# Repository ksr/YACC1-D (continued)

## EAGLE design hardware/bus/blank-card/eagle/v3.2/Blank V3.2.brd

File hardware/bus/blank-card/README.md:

# bus/blank-card

Starting point for a new card: the bus connector(s), card outline and mounting, with every bus signal named.
`eagle/v3.1/` (2020-08-23) = the Bus Template V3.1 schematic on the card outline; ordered 2025-06-27 as a bare
board (zip + Fusion CAM output in `fab/`) and used as the base of the video card.

**Caution:** it carries the Bus V3.1 signal names, i.e. C3–C6 are labelled -ADDR-REG-RD0/LD0/RD1/LD1. The machine
is built to Bus V3.2, where those pins are ADDR-REG-ID0..3 (see `hardware/FABRICATED.md` notes and
`docs/system/`). Any card drawn on this template inherits the stale names (Mem Switch, Mem Register and the video
card did). `eagle/v3.2/` (derived 2026-09-20, see its README) is V3.1 with those four nets renamed to the V3.2 names: **start new cards from V3.2.**

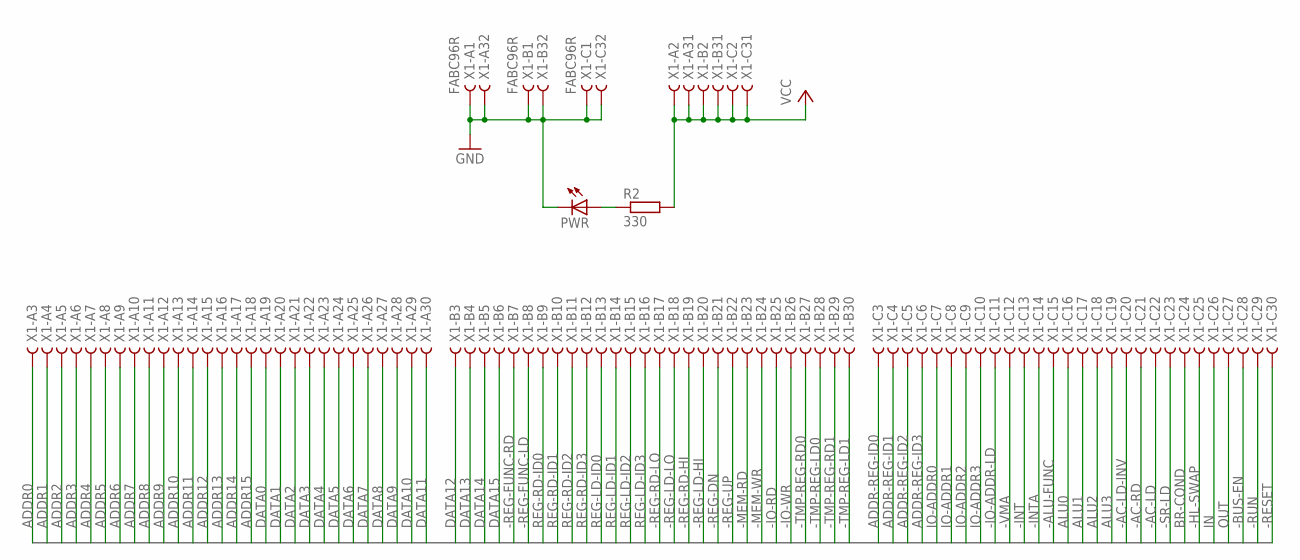
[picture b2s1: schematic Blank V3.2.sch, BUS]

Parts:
PWR: LED5MM
R2: 330; 0207/10
X1: FABC96R

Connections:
-AC-LD: X1.C22
-AC-LD-INV: X1.C20
-AC-RD: X1.C21
-ALU-FUNC: X1.C15
-BUS-EN: X1.C28
-HL-SWAP: X1.C25
-INT: X1.C13
-INTA: X1.C14
-IO-ADDR-LD: X1.C11
-IO-RD: X1.B25
-IO-WR: X1.B26
-MEM-RD: X1.B23
-MEM-WR: X1.B24
-REG-DN: X1.B21
-REG-FUNC-LD: X1.B8
-REG-FUNC-RD: X1.B7
-REG-LD-HI: X1.B20
-REG-LD-LO: X1.B18
-REG-RD-HI: X1.B19
-REG-RD-LO: X1.B17
-REG-UP: X1.B22
-RESET: X1.C30
-RUN: X1.C29
-SR-LD: X1.C23
-TMP-REG-LD0: X1.B28
-TMP-REG-LD1: X1.B30
-TMP-REG-RD0: X1.B27
-TMP-REG-RD1: X1.B29
-VMA: X1.C12
ADDR0: X1.A3
ADDR1: X1.A4
ADDR2: X1.A5
ADDR3: X1.A6
ADDR4: X1.A7
ADDR5: X1.A8
ADDR6: X1.A9
ADDR7: X1.A10
ADDR8: X1.A11
ADDR9: X1.A12
ADDR10: X1.A13
ADDR11: X1.A14
ADDR12: X1.A15
ADDR13: X1.A16
ADDR14: X1.A17
ADDR15: X1.A18
ADDR-REG-ID0: X1.C3
ADDR-REG-ID1: X1.C4
ADDR-REG-ID2: X1.C5
ADDR-REG-ID3: X1.C6
ALU0: X1.C16
ALU1: X1.C17
ALU2: X1.C18
ALU3: X1.C19
BR-COND: X1.C24
DATA0: X1.A19
DATA1: X1.A20
DATA2: X1.A21
DATA3: X1.A22
DATA4: X1.A23
DATA5: X1.A24
DATA6: X1.A25
DATA7: X1.A26
DATA8: X1.A27
DATA9: X1.A28
DATA10: X1.A29
DATA11: X1.A30
DATA12: X1.B3
DATA13: X1.B4
DATA14: X1.B5
DATA15: X1.B6
GND: PWR.K (C), X1.A1, X1.A32, X1.B1, X1.B32, X1.C1, X1.C32
IN: X1.C26
IO-ADDR0: X1.C7
IO-ADDR1: X1.C8
IO-ADDR2: X1.C9
IO-ADDR3: X1.C10
unnamed: PWR.A, R2.1
OUT: X1.C27
REG-LD-ID0: X1.B13
REG-LD-ID1: X1.B14
REG-LD-ID2: X1.B15
REG-LD-ID3: X1.B16
REG-RD-ID0: X1.B9
REG-RD-ID1: X1.B10
REG-RD-ID2: X1.B11
REG-RD-ID3: X1.B12
VCC: R2.2, X1.A2, X1.A31, X1.B2, X1.B31, X1.C2, X1.C31

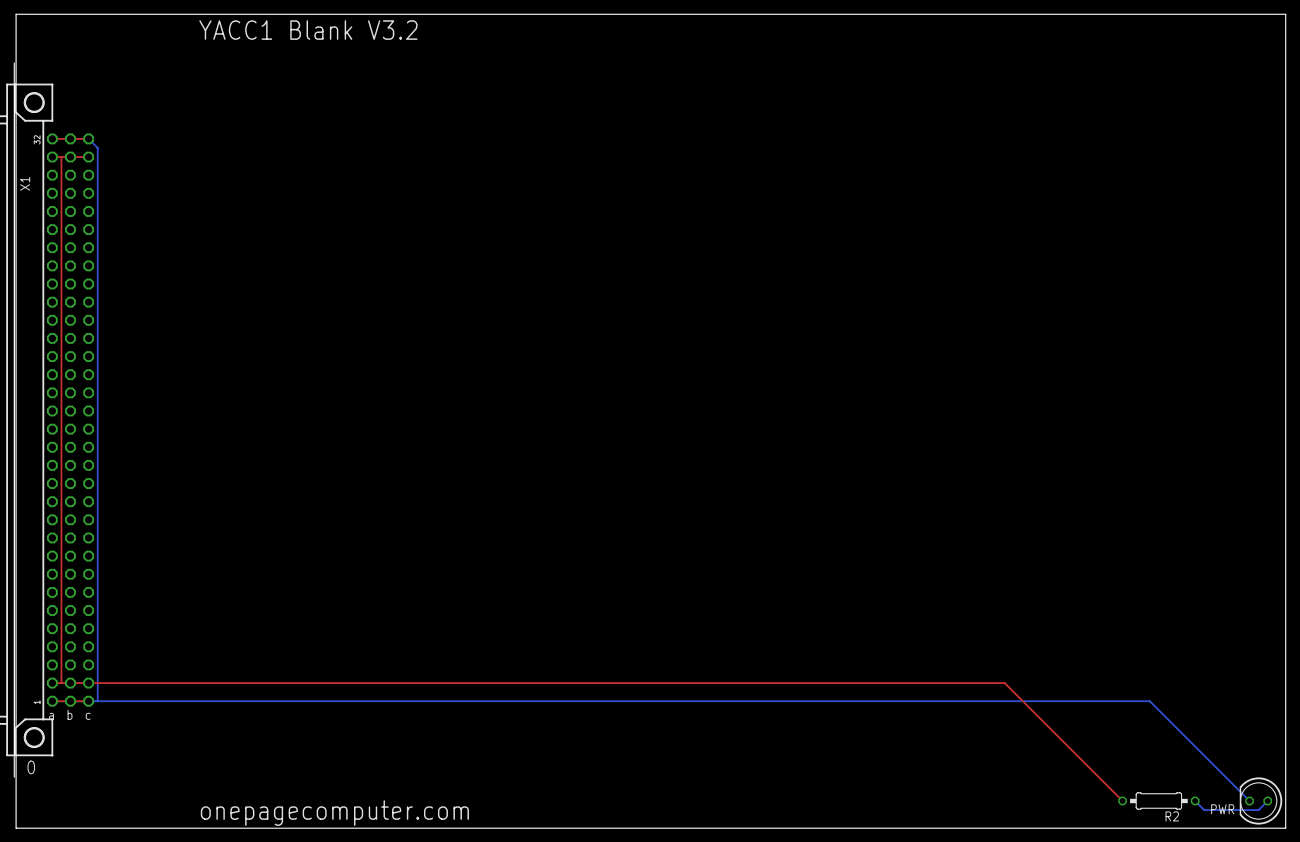
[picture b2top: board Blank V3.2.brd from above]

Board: 2 copper layers, 177.8 x 114.0 mm, 3 parts (0 on the bottom side), 3 nets.

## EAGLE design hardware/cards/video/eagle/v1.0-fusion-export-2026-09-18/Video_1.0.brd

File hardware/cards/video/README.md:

# cards/video — Video card (memory-mapped alphanumeric display)

MC6845 CRTC + IDT7134 dual-port RAM. The CPU sees 2K: the low half is display RAM (A11R grounded), the high
half addresses the CRTC. Decoded by a 7485 comparator against jumpers SV3 (installed = 0, open = 1; $D000 needs
only SV3 5–6), cascaded from -VMA, into the memory card's undecoded $D000 block. Character ROM, dot clock
and sync on the card; the LM1881 sync-converter Eagle project in `archive/eagle-projects/` is the related
composite-video experiment.

**KiCad is the master design: `kicad/v2.0/` (2026-10-22, generated from `v20_netlist.py` by `gen_v20.py` / `build.sh`;
`kicad/v1.3/`, `kicad/v1.2/` and `kicad/v1.1/` before it) — Fusion 360 abandoned for this card.**
`eagle/v1.0-fusion-export-2026-09-18/` is the Fusion export of the BUILT card (`Video_1.0.sch/.brd`, exported by Fusion as
"Blank V3.1.brd" because the design started from the blank template) and `kicad/v1.0-fusion-export-2026-09-18/` its
generated, proven conversion; both are the record of what was built. One version built, in the machine for bring-up
since 2026-10-21 with a CRTC and working. v1.1: the two 5 V nets merged into `VCC` with a joining track. v1.2 (not
ordered): v1.1 plus every bench fix up to 2026-10-21 - RS on ADDR1, LPSTB to GND, 4.7k pull-ups on N$16 and N$5 (R13,
R14), E straight from the strobe (the R1/C1 one-shot removed), IC28 a 74163, Q2 11.0592 MHz (see its README). v1.3 (not
ordered): 6 or 8 dots a character chosen by one jumper (DOTS, JP2: 80 x 24 or 64 x 24 from a 12 MHz crystal, both fonts
in one EPROM, the mode readable at `$D801` bit 0, the card ID on bit 2 = 0: latch 3D tied low; the card in the
machine reads bit 2 = 1 through a jumper on JP1 3-4; `ROM 2026-10-22` picks its geometry from them), on a new 4-layer board (In1 GND plane, In2 VCC plane) routed from
scratch (`kicad/v1.3/README.md`, `build.sh`). **V2.0** (not ordered): v1.3 plus a graphics layer (512 x 192 in 8-dot mode,
a time-shared 62256 behind the window $D800-$DFFF), the 6845 and every register on I/O ports PA-PE, two PS/2 ports on an
ATmega328P (`embedded/video-ps2`) and an INT jumper; 218 mm long, 4 layers (`kicad/v2.0/README.md`, `docs/cards/video-v2.md`).

Known issues and findings:
- **+5V rail unpowered as designed (found 2026-09-20 by the KiCad netlist proof, confirmed on the bench 2026-09-21).**
  The design has two 5 V nets with nothing joining them: `VCC` (bus pins, the implicit power pins of IC17–IC28) and `+5V`
  (IC1 74ALS08, IC2 74LS373, IC15 pin 2, RN2, R10, R12 and every decoupling cap). `+5V` reaches no connector pin, so IC1,
  IC2 and the SV3 pull-ups ran on phantom power through input clamp diodes. The two rails were joined with a wire
  (2026-09-21); after that the write-through fault below was gone. The KiCad conversion's `reports/netlist-compare.txt`
  shows the two nets.
- **Write-through fault — RESOLVED 2026-09-21.** On 2026-09-18 a write to block 0 or block 9 (A0 = 0, A11 = 0, -MEM-WR
  falling edge, -VMA asserted) landed in the video RAM regardless of the board-select comparator. Cause: the unpowered
  `+5V` rail (IC1 drives BOARDSEL into the 7485, RN2 pulls the SV3 jumper inputs up to that rail). With the rails joined,
  `tests/video/video_ram_test.py` passes 8/8 over all 1K (patterns, inverse, neighbour isolation, writes from $0010/$9010/
  $0011/$1010 never reach $D010, read stability) and `tools/alias_min.py` reports no fault.
- **6845 data register unreachable as drawn.** -CS (IC17 pin 25) = NAND(BOARDSEL, A11 AND /A0): IC19 pin 3, from IC1 pin 11
  (A11 AND N$5) where N$5 = IC27 pin 8 = /A0. RS is A0. So the chip is only selected with A0 = 0, which is always RS = 0:
  only the address register is reachable, the data register never. Bench fix: lift IC1 pin 13 off IC27 pin 8 and tie it
  high is WRONG (odd addresses drive the JP1 read-back latch IC2 onto the bus). Correct fix: move RS from A0 to A1 —
  pin-by-pin procedure in `docs/fix-6845-register-select.md`; then $D800 = address register, $D802 = data register (video RAM $D000-$D7FF, 6845 half $D800-$DFFF; confirmed 2026-09-25).
- 7416 open-collector outputs (IC27) drive IC1, IC2 and IC26 with no pull-ups; N$5 above only reads high when floating. 4.7k pull-ups fitted on the bench 2026-10-21: IC2 pin 1 to pin 20 (N$16, the latch's -OC) and IC27 pin 8 to pin 14 (N$5, /A0); the 10k on IC27 pin 12 (N$3) covers the E one-shot.
- Inherits the Blank V3.1 template's pre-V3.2 names on bus pins C3–C6 (unused by the card).

Bench state: RN2 back to the design's 10k (2026-09-21; it had been 1k since the 2026-09-18 tests — with the rail
unpowered the value never mattered; quick RAM test 8/8 with 10k); +5V and VCC joined by a wire (2026-09-21). Since 2026-10-21: the MC6845 fitted (RS on A1, LPSTB to GND),
an 11.0592 MHz crystal in Q2 (SV4 1-2; 9 MHz first, which fits only 64 columns), the pull-ups above, IC2 a 74LS373; an 80 x 24 picture with the CPU out
(`docs/procedures/VIDEO-BRINGUP.md`).

Reference: `docs/BYTE 6845.pdf` - a BYTE magazine article on the 6845 CRTC (a personal copy, added 2026-09-26).

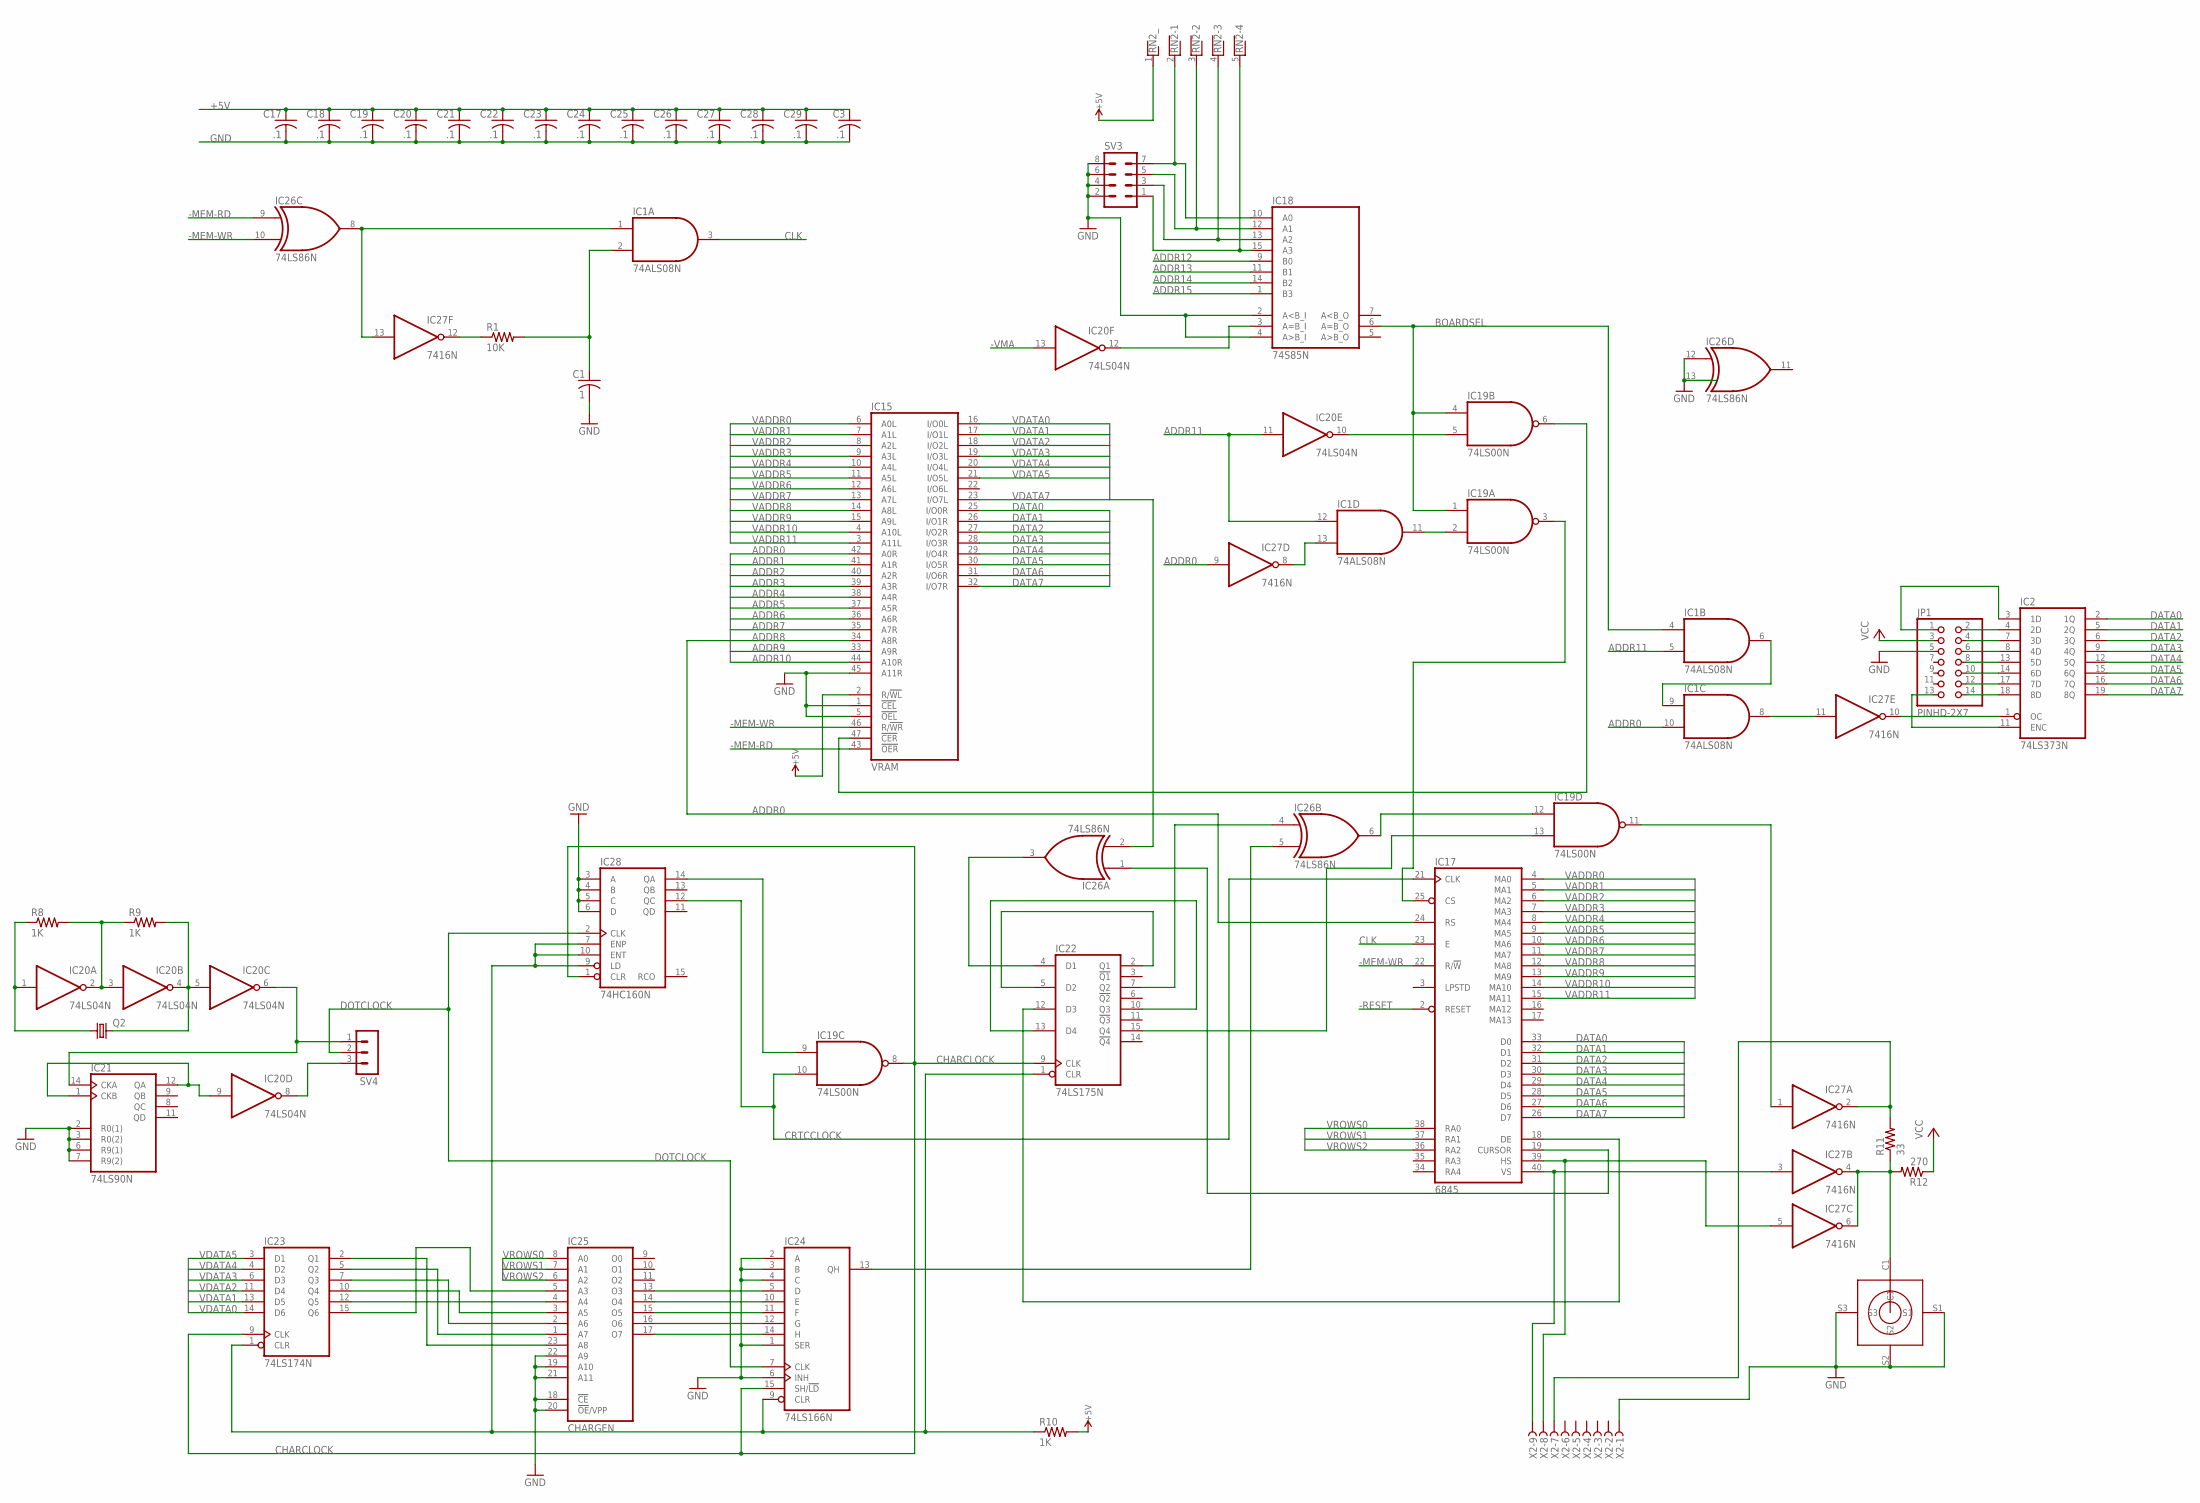
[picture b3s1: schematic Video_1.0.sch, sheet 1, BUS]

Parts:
C1: 1; C025-050X050
C3, C17, C18, C19, C20, C21, C22, C23, C24, C25, C26, C27, C28, C29: .1; C025-050X050
IC1: 74ALS08N; DIL14
IC2: 74LS373N; DIL20
IC15: VRAM; DIL48
IC17: 6845; DIL40
IC18: 74S85N; DIL16
IC19: 74LS00N; DIL14
IC20: 74LS04N; DIL14
IC21: 74LS90N; DIL14
IC22: 74LS175N; DIL16
IC23: 74LS174N; DIL16
IC24: 74LS166N; DIL16
IC25: CHARGEN; DIL24
IC26: 74LS86N; DIL14
IC27: 7416N; DIL14
IC28: 74HC160N; DIL16
JP1: PINHD-2X7; 2X07
Q2: CRYTALHC49U-V; HC49U-V
R1: 10K; 0207/7
R8, R9, R10: 1K; 0207/7
R11: 33; 0207/7
R12: 270; 0207/7
RN2: RNX4; RN-5
SV3: MA04-2
SV4: MA03-1
U$3: RCA
X2: F09HPS; F09HP

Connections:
+5V: C3.1, C17.1, C18.1, C19.1, C20.1, C21.1, C22.1, C23.1, C24.1, C25.1, C26.1, C27.1, C28.1, C29.1, IC1.14 (VCC), IC2.20 (VCC), IC15.2 (R/!WL), R10.2, R12.1, RN2.1; also elsewhere on the board
-MEM-RD: IC15.43 (!OER), IC26.9 (I0); also elsewhere on the board
-MEM-WR: IC15.46 (R/!WR), IC17.22 (R/!W), IC26.10 (I1); also elsewhere on the board
-RESET: IC17.2 (RESET); also elsewhere on the board
-VMA: IC20.13 (I); also elsewhere on the board
ADDR0: IC1.10 (I1), IC15.42 (A0R), IC17.24 (RS), IC27.9 (I); also elsewhere on the board
ADDR1: IC15.41 (A1R); also elsewhere on the board
ADDR2: IC15.40 (A2R); also elsewhere on the board
ADDR3: IC15.39 (A3R); also elsewhere on the board
ADDR4: IC15.38 (A4R); also elsewhere on the board
ADDR5: IC15.37 (A5R); also elsewhere on the board
ADDR6: IC15.36 (A6R); also elsewhere on the board
ADDR7: IC15.35 (A7R); also elsewhere on the board
ADDR8: IC15.34 (A8R); also elsewhere on the board
ADDR9: IC15.33 (A9R); also elsewhere on the board
ADDR10: IC15.44 (A10R); also elsewhere on the board
ADDR11: IC1.5 (I1), IC1.12 (I0), IC20.11 (I); also elsewhere on the board
ADDR12: IC18.9 (B0); also elsewhere on the board
ADDR13: IC18.11 (B1); also elsewhere on the board
ADDR14: IC18.14 (B2); also elsewhere on the board
ADDR15: IC18.1 (B3); also elsewhere on the board
BOARDSEL: IC1.4 (I0), IC18.6 (A=B_O), IC19.1 (I0), IC19.4 (I0)
CHARCLOCK: IC19.8 (O), IC22.9 (CLK), IC23.9 (CLK), IC24.15 (SH/!LD), IC28.1 (CLR)
CLK: IC1.3 (O), IC17.23 (E)
CRTCCLOCK: IC17.21 (CLK), IC19.10 (I1), IC28.12 (QC)
DATA0: IC2.2 (1Q), IC15.25 (I/O0R), IC17.33 (D0); also elsewhere on the board
DATA1: IC2.5 (2Q), IC15.26 (I/O1R), IC17.32 (D1); also elsewhere on the board
DATA2: IC2.6 (3Q), IC15.27 (I/O2R), IC17.31 (D2); also elsewhere on the board
DATA3: IC2.9 (4Q), IC15.28 (I/O3R), IC17.30 (D3); also elsewhere on the board
DATA4: IC2.12 (5Q), IC15.29 (I/O4R), IC17.29 (D4); also elsewhere on the board
DATA5: IC2.15 (6Q), IC15.30 (I/O5R), IC17.28 (D5); also elsewhere on the board
DATA6: IC2.16 (7Q), IC15.31 (I/O6R), IC17.27 (D6); also elsewhere on the board
DATA7: IC2.19 (8Q), IC15.32 (I/O7R), IC17.26 (D7); also elsewhere on the board
DOTCLOCK: IC24.7 (CLK), IC28.2 (CLK), SV4.2
GND: C1.2, C3.2, C17.2, C18.2, C19.2, C20.2, C21.2, C22.2, C23.2, C24.2, C25.2, C26.2, C27.2, C28.2, C29.2, IC1.7 (GND), IC2.10 (GND), IC15.1 (!CEL), IC15.5 (!OEL), IC15.24 (GND), IC15.45 (A11R), IC17.1 (GND), IC18.2 (A<B_I), IC18.4 (A>B_I), IC18.8 (GND), IC19.7 (GND), IC20.7 (GND), IC21.2 (R0(1)), IC21.3 (R0(2)), IC21.6 (R9(1)), IC21.7 (R9(2)), IC21.10 (GND), IC22.8 (GND), IC23.8 (GND), IC24.1 (SER), IC24.2 (A), IC24.3 (B), IC24.4 (C), IC24.6 (INH), IC24.8 (GND), IC25.12 (GND), IC25.18 (!CE), IC25.19 (A10), IC25.20 (!OE!/VPP), IC25.21 (A11), IC25.22 (A9), IC26.7 (GND), IC26.12 (I0), IC26.13 (I1), IC27.7 (GND), IC28.3 (A), IC28.4 (B), IC28.5 (C), IC28.6 (D), IC28.8 (GND), JP1.5, SV3.2, SV3.4, SV3.6, SV3.8, U$3.S1, U$3.S2, U$3.S3, X2.1; also elsewhere on the board
unnamed: IC1.1 (I0), IC26.8 (O), IC27.13 (I)
unnamed: IC1.11 (O), IC19.2 (I1)
unnamed: IC27.12 (O), R1.1
unnamed: C1.1, IC1.2 (I1), R1.2
unnamed: IC1.13 (I1), IC27.8 (O)
unnamed: IC1.8 (O), IC27.11 (I)
unnamed: IC2.18 (8D), JP1.14
unnamed: IC2.17 (7D), JP1.12
unnamed: IC2.14 (6D), JP1.10
unnamed: IC2.13 (5D), JP1.8
unnamed: IC2.8 (4D), JP1.6
unnamed: IC2.7 (3D), JP1.4
unnamed: IC2.4 (2D), JP1.2
unnamed: IC2.3 (1D), JP1.1
unnamed: IC2.1 (OC), IC27.10 (O)
unnamed: IC1.6 (O), IC1.9 (I0)
unnamed: IC2.11 (ENC), JP1.13
unnamed: IC18.10 (A0), RN2.2, SV3.7
unnamed: IC18.12 (A1), RN2.3, SV3.5
unnamed: IC18.13 (A2), RN2.4, SV3.3
unnamed: IC18.15 (A3), RN2.5, SV3.1
unnamed: IC15.47 (!CER), IC19.6 (O)
unnamed: IC20.1 (I), Q2.1, R8.1
unnamed: IC20.4 (O), IC20.5 (I), Q2.2, R9.2
unnamed: IC20.2 (O), IC20.3 (I), R8.2, R9.1
unnamed: IC20.6 (O), IC21.14 (CKA), SV4.1
unnamed: IC20.9 (I), IC21.1 (CKB), IC21.12 (QA)
unnamed: IC20.8 (O), SV4.3
unnamed: IC19.9 (I0), IC28.14 (QA)
unnamed: IC22.2 (Q1), IC22.5 (D2)
unnamed: IC24.5 (D), IC25.13 (O3)
unnamed: IC24.10 (E), IC25.14 (O4)
unnamed: IC24.11 (F), IC25.15 (O5)
unnamed: IC24.12 (G), IC25.16 (O6)
unnamed: IC24.14 (H), IC25.17 (O7)
unnamed: IC23.2 (Q1), IC25.23 (A8)
unnamed: IC23.5 (Q2), IC25.1 (A7)
unnamed: IC23.7 (Q3), IC25.2 (A6)
unnamed: IC23.10 (Q4), IC25.3 (A5)
unnamed: IC23.12 (Q5), IC25.4 (A4)
unnamed: IC23.15 (Q6), IC25.5 (A3)
unnamed: IC22.1 (CLR), IC23.1 (CLR), IC24.9 (CLR), IC28.7 (ENP), IC28.9 (LD), IC28.10 (ENT), R10.1
unnamed: IC17.19 (CURSOR), IC26.1 (I0)
unnamed: IC22.4 (D1), IC26.3 (O)
unnamed: IC22.7 (Q2), IC26.4 (I0)
unnamed: IC24.13 (QH), IC26.5 (I1)
unnamed: IC22.10 (Q3), IC22.13 (D4)
unnamed: IC17.18 (DE), IC22.12 (D3)
unnamed: IC19.12 (I0), IC26.6 (O)
unnamed: IC19.13 (I1), IC22.15 (Q4)
unnamed: IC17.40 (VS), IC27.3 (I), X2.9
unnamed: IC17.39 (HS), IC27.5 (I), X2.8
unnamed: IC19.11 (O), IC27.1 (I)
unnamed: IC27.4 (O), IC27.6 (O), R11.1, R12.2, U$3.C1
unnamed: IC27.2 (O), R11.2, X2.7
unnamed: IC19.5 (I1), IC20.10 (O)
unnamed: IC18.3 (A=B_I), IC20.12 (O)
unnamed: IC17.25 (CS), IC19.3 (O)
VADDR0: IC15.6 (A0L), IC17.4 (MA0)
VADDR1: IC15.7 (A1L), IC17.5 (MA1)
VADDR2: IC15.8 (A2L), IC17.6 (MA2)
VADDR3: IC15.9 (A3L), IC17.7 (MA3)
VADDR4: IC15.10 (A4L), IC17.8 (MA4)
VADDR5: IC15.11 (A5L), IC17.9 (MA5)
VADDR6: IC15.12 (A6L), IC17.10 (MA6)
VADDR7: IC15.13 (A7L), IC17.11 (MA7)
VADDR8: IC15.14 (A8L), IC17.12 (MA8)
VADDR9: IC15.15 (A9L), IC17.13 (MA9)
VADDR10: IC15.4 (A10L), IC17.14 (MA10)
VADDR11: IC15.3 (A11L), IC17.15 (MA11)
VCC: IC15.48 (VCC), IC17.20 (VCC), IC18.16 (VCC), IC19.14 (VCC), IC20.14 (VCC), IC21.5 (VCC), IC22.16 (VCC), IC23.16 (VCC), IC24.16 (VCC), IC25.24 (VCC), IC26.14 (VCC), IC27.14 (VCC), IC28.16 (VCC), JP1.3; also elsewhere on the board
VDATA0: IC15.16 (I/O0L), IC23.14 (D6)
VDATA1: IC15.17 (I/O1L), IC23.13 (D5)
VDATA2: IC15.18 (I/O2L), IC23.11 (D4)
VDATA3: IC15.19 (I/O3L), IC23.6 (D3)
VDATA4: IC15.20 (I/O4L), IC23.4 (D2)
VDATA5: IC15.21 (I/O5L), IC23.3 (D1)
VDATA7: IC15.23 (I/O7L), IC26.2 (I1)
VROWS0: IC17.38 (RA0), IC25.8 (A0)
VROWS1: IC17.37 (RA1), IC25.7 (A1)
VROWS2: IC17.36 (RA2), IC25.6 (A2)

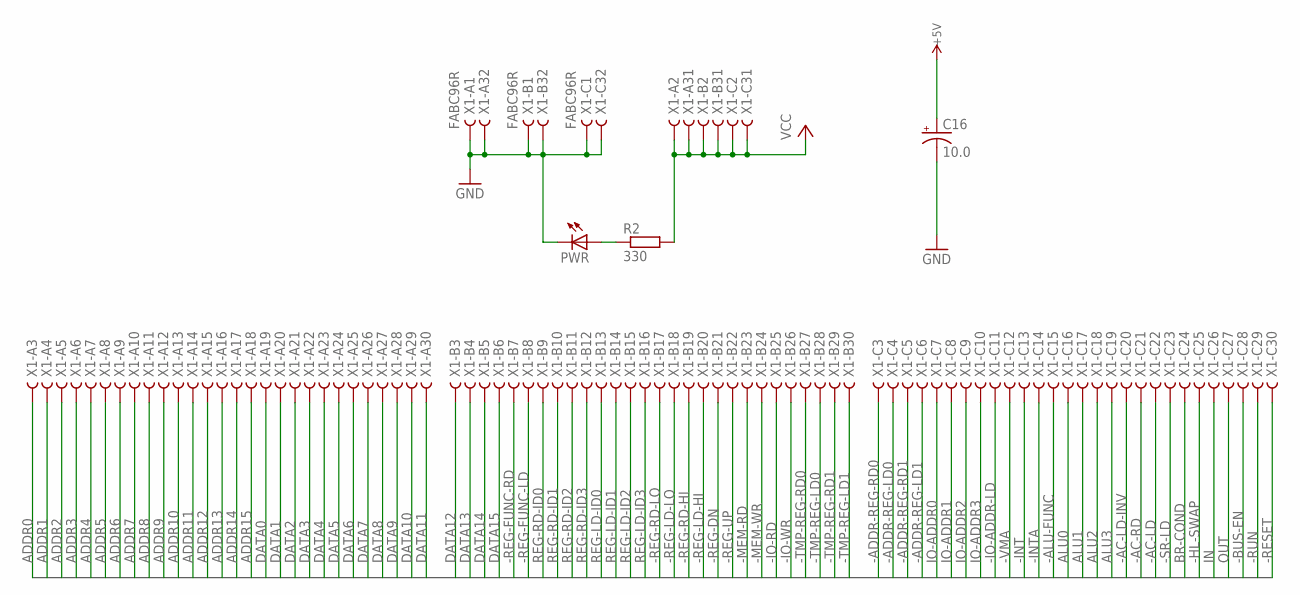
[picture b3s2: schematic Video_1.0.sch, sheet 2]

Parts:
C16: 10.0; E2,5-7
PWR: LED5MM
R2: 330; 0207/10
X1: FABC96R

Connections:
+5V: C16.+; also elsewhere on the board
-AC-LD: X1.C22
-AC-LD-INV: X1.C20
-AC-RD: X1.C21
-ADDR-REG-LD0: X1.C4
-ADDR-REG-LD1: X1.C6
-ADDR-REG-RD0: X1.C3
-ADDR-REG-RD1: X1.C5
-ALU-FUNC: X1.C15
-BUS-EN: X1.C28
-HL-SWAP: X1.C25
-INT: X1.C13
-INTA: X1.C14
-IO-ADDR-LD: X1.C11
-IO-RD: X1.B25
-IO-WR: X1.B26
-MEM-RD: X1.B23; also elsewhere on the board
-MEM-WR: X1.B24; also elsewhere on the board
-REG-DN: X1.B21
-REG-FUNC-LD: X1.B8
-REG-FUNC-RD: X1.B7
-REG-LD-HI: X1.B20
-REG-LD-LO: X1.B18
-REG-RD-HI: X1.B19
-REG-RD-LO: X1.B17
-REG-UP: X1.B22
-RESET: X1.C30; also elsewhere on the board
-RUN: X1.C29
-SR-LD: X1.C23
-TMP-REG-LD0: X1.B28
-TMP-REG-LD1: X1.B30
-TMP-REG-RD0: X1.B27
-TMP-REG-RD1: X1.B29
-VMA: X1.C12; also elsewhere on the board
ADDR0: X1.A3; also elsewhere on the board
ADDR1: X1.A4; also elsewhere on the board
ADDR2: X1.A5; also elsewhere on the board
ADDR3: X1.A6; also elsewhere on the board
ADDR4: X1.A7; also elsewhere on the board
ADDR5: X1.A8; also elsewhere on the board
ADDR6: X1.A9; also elsewhere on the board
ADDR7: X1.A10; also elsewhere on the board
ADDR8: X1.A11; also elsewhere on the board
ADDR9: X1.A12; also elsewhere on the board
ADDR10: X1.A13; also elsewhere on the board
ADDR11: X1.A14; also elsewhere on the board
ADDR12: X1.A15; also elsewhere on the board
ADDR13: X1.A16; also elsewhere on the board
ADDR14: X1.A17; also elsewhere on the board
ADDR15: X1.A18; also elsewhere on the board
ALU0: X1.C16
ALU1: X1.C17
ALU2: X1.C18
ALU3: X1.C19
BR-COND: X1.C24
DATA0: X1.A19; also elsewhere on the board
DATA1: X1.A20; also elsewhere on the board
DATA2: X1.A21; also elsewhere on the board
DATA3: X1.A22; also elsewhere on the board
DATA4: X1.A23; also elsewhere on the board
DATA5: X1.A24; also elsewhere on the board
DATA6: X1.A25; also elsewhere on the board
DATA7: X1.A26; also elsewhere on the board
DATA8: X1.A27
DATA9: X1.A28
DATA10: X1.A29
DATA11: X1.A30
DATA12: X1.B3
DATA13: X1.B4
DATA14: X1.B5
DATA15: X1.B6
GND: C16.-, PWR.K (C), X1.A1, X1.A32, X1.B1, X1.B32, X1.C1, X1.C32; also elsewhere on the board
IN: X1.C26
IO-ADDR0: X1.C7
IO-ADDR1: X1.C8
IO-ADDR2: X1.C9
IO-ADDR3: X1.C10
unnamed: PWR.A, R2.1
OUT: X1.C27
REG-LD-ID0: X1.B13
REG-LD-ID1: X1.B14
REG-LD-ID2: X1.B15
REG-LD-ID3: X1.B16
REG-RD-ID0: X1.B9
REG-RD-ID1: X1.B10
REG-RD-ID2: X1.B11
REG-RD-ID3: X1.B12
VCC: R2.2, X1.A2, X1.A31, X1.B2, X1.B31, X1.C2, X1.C31; also elsewhere on the board

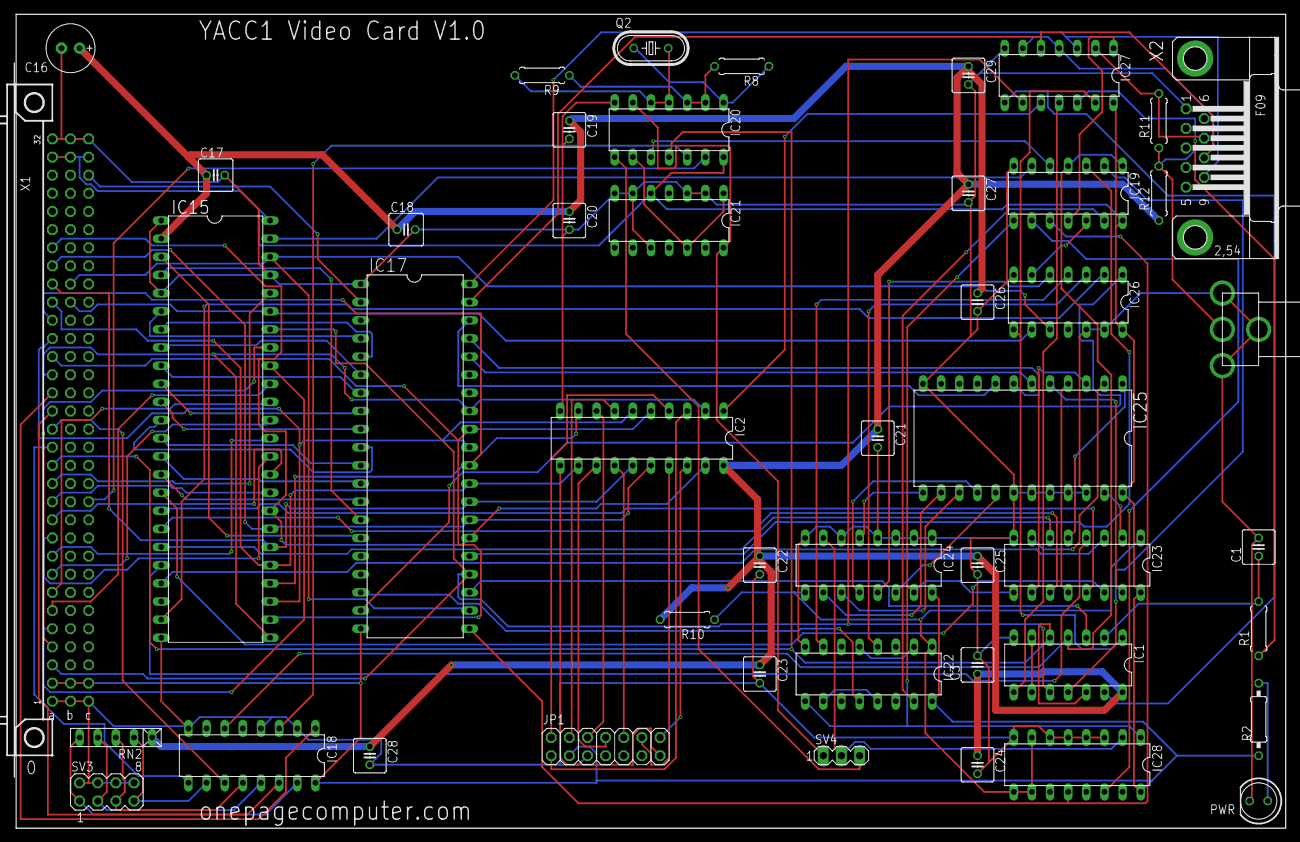
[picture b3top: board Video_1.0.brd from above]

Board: 2 copper layers, 177.8 x 114.0 mm, 47 parts (0 on the bottom side), 117 nets.
